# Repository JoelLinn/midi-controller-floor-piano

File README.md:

# midi-controller-floor-piano
Converts your awful sounding floor piano into a midi keyboard controller you can hook up to your synthesizers.
It uses an ARM NXP LPC1113 MCU which is hopelessly overpowered but still quite cheap.

Fits where the stock board belonged and supports the original battery, buttons and leds.
The firmware, although working great, is merely in a POC state so I would prefer to hand it out only on request.

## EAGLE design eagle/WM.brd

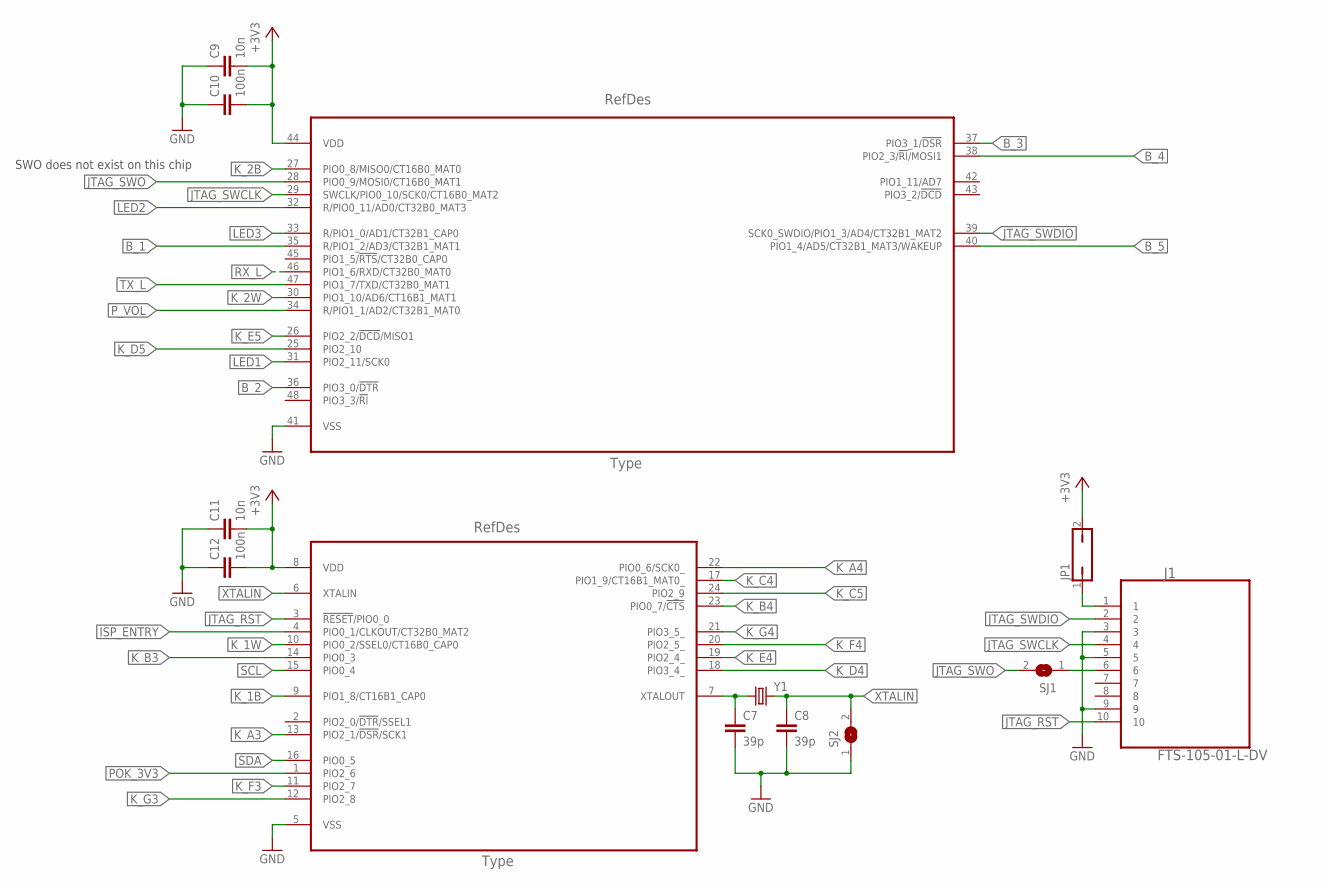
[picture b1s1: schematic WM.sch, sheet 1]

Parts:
C7, C8: 39p; C0805
C9, C11: 10n; C0805
C10, C12: 100n; C0805
J1: FTS-105-01-L-DV; SAMTEC_FTS-105-01-L-DV
JP1: JP1Q; JP1
SJ1, SJ2: SJ
U1: LPC1113FBD48/302,1; QFP50P900X900X160-48N
Y1: CRYSTALHC49UP; HC49UP

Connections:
+3V3: C9.2, C10.2, C11.2, C12.2, JP1.2, U1.8 (VDD), U1.44 (VDD); also elsewhere on the board
B_1: U1.35 (R/PIO1_2/AD3/CT32B1_MAT1); also elsewhere on the board
B_2: U1.36 (PIO3_0/!DTR!); also elsewhere on the board
B_3: U1.37 (PIO3_1/!DSR!); also elsewhere on the board
B_4: U1.38 (PIO2_3/!RI!/MOSI1); also elsewhere on the board
B_5: U1.40 (PIO1_4/AD5/CT32B1_MAT3/WAKEUP); also elsewhere on the board
GND: C7.2, C8.2, C9.1, C10.1, C11.1, C12.1, J1.3, J1.5, J1.9, SJ2.1, U1.5 (VSS), U1.41 (VSS); also elsewhere on the board
ISP_ENTRY: U1.4 (PIO0_1/CLKOUT/CT32B0_MAT2)
JTAG_RST: J1.10, U1.3 (!RESET!/PIO0_0)
JTAG_SWCLK: J1.4, U1.29 (SWCLK/PIO0_10/SCK0/CT16B0_MAT2)
JTAG_SWDIO: J1.2, U1.39 (SCK0_SWDIO/PIO1_3/AD4/CT32B1_MAT2)
JTAG_SWO: SJ1.2, U1.28 (PIO0_9/MOSI0/CT16B0_MAT1)
K_1B: U1.9 (PIO1_8/CT16B1_CAP0); also elsewhere on the board
K_1W: U1.10 (PIO0_2/SSEL0/CT16B0_CAP0); also elsewhere on the board
K_2B: U1.27 (PIO0_8/MISO0/CT16B0_MAT0); also elsewhere on the board
K_2W: U1.30 (PIO1_10/AD6/CT16B1_MAT1); also elsewhere on the board
K_A3: U1.13 (PIO2_1/!DSR!/SCK1); also elsewhere on the board
K_A4: U1.22 (PIO0_6/SCK0_); also elsewhere on the board
K_B3: U1.14 (PIO0_3); also elsewhere on the board
K_B4: U1.23 (PIO0_7/!CTS!); also elsewhere on the board
K_C4: U1.17 (PIO1_9/CT16B1_MAT0_); also elsewhere on the board
K_C5: U1.24 (PIO2_9); also elsewhere on the board
K_D4: U1.18 (PIO3_4_); also elsewhere on the board
K_D5: U1.25 (PIO2_10); also elsewhere on the board
K_E4: U1.19 (PIO2_4_); also elsewhere on the board
K_E5: U1.26 (PIO2_2/!DCD!/MISO1); also elsewhere on the board
K_F3: U1.11 (PIO2_7); also elsewhere on the board
K_F4: U1.20 (PIO2_5_); also elsewhere on the board
K_G3: U1.12 (PIO2_8); also elsewhere on the board
K_G4: U1.21 (PIO3_5_); also elsewhere on the board
LED1: U1.31 (PIO2_11/SCK0); also elsewhere on the board
LED2: U1.32 (R/PIO0_11/AD0/CT32B0_MAT3); also elsewhere on the board
LED3: U1.33 (R/PIO1_0/AD1/CT32B1_CAP0); also elsewhere on the board
unnamed: C7.1, U1.7 (XTALOUT), Y1.1
unnamed: J1.1, JP1.1
unnamed: J1.6, SJ1.1
POK_3V3: U1.1 (PIO2_6); also elsewhere on the board
P_VOL: U1.34 (R/PIO1_1/AD2/CT32B1_MAT0); also elsewhere on the board
RX_L: U1.46 (PIO1_6/RXD/CT32B0_MAT0); also elsewhere on the board
SCL: U1.15 (PIO0_4); also elsewhere on the board
SDA: U1.16 (PIO0_5); also elsewhere on the board
TX_L: U1.47 (PIO1_7/TXD/CT32B0_MAT1); also elsewhere on the board
XTALIN: C8.1, SJ2.2, U1.6 (XTALIN), Y1.2

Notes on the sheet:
SWO does not exist on this chip

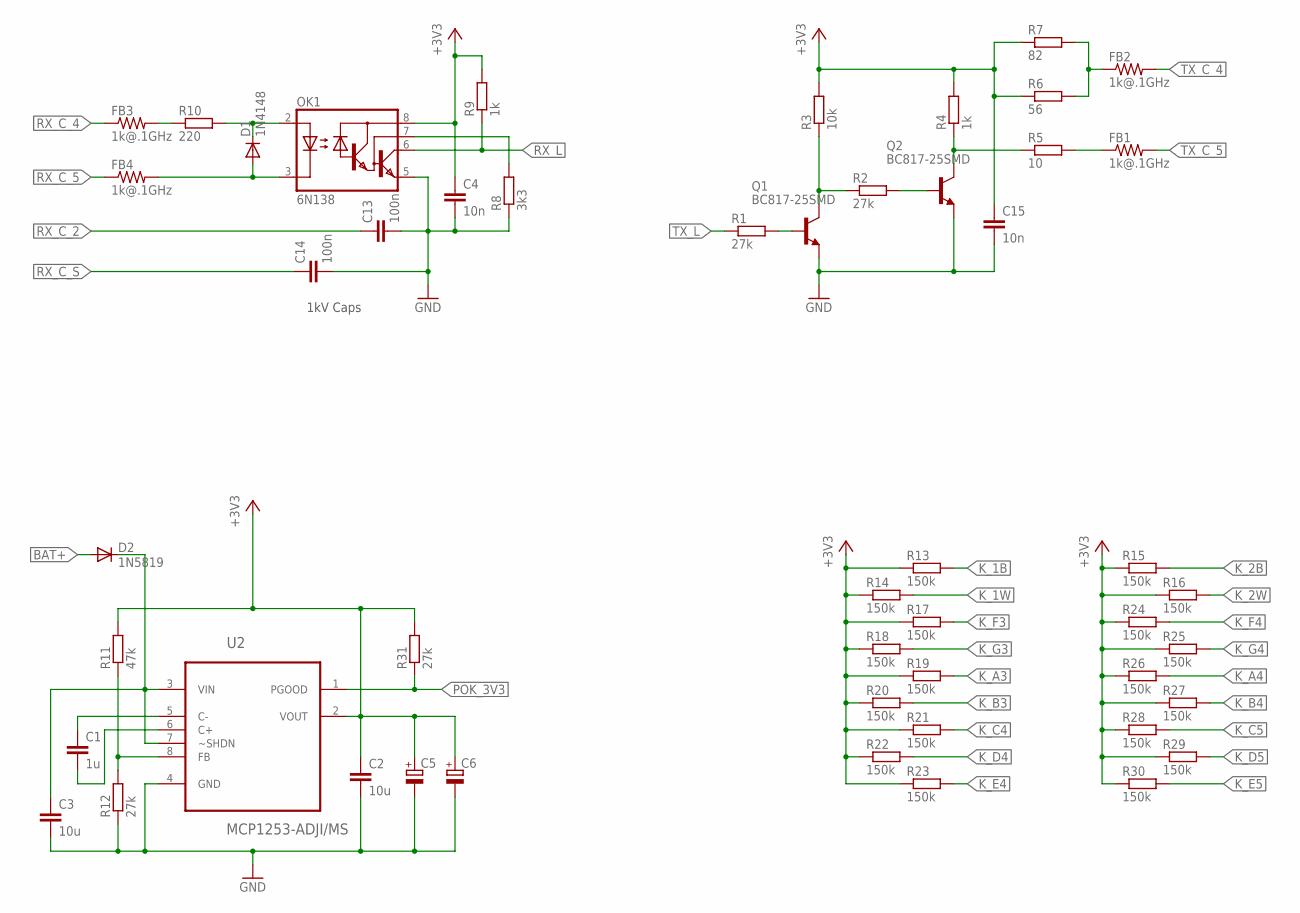
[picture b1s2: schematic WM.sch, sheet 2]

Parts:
C1: 1u; C0805
C2, C3: 10u; C0805
C4, C15: 10n; C0805
C5, C6: CPOL-EUE2.5-6; E2,5-6
C13, C14: 100n; C1210K
D1: 1N4148; SOD323-R
D2: 1N5819; SOD123
FB1, FB2, FB3, FB4: 1k@.1GHz; R0805
OK1: 6N138; DIL08
Q1, Q2: BC817-25SMD; SOT23-BEC
R1, R2, R12, R31: 27k; R0805
R3: 10k; R0805
R4, R9: 1k; R0805
R5: 10; R0805
R6: 56; R0805
R7: 82; R0805
R8: 3k3; R0805
R10: 220; R0805
R11: 47k; R0805
R13, R14, R15, R16, R17, R18, R19, R20, R21, R22, R23, R24, R25, R26, R27, R28, R29, R30: 150k; R0805
U2: MCP1253-ADJI/MS; SOP65P490X118-8N

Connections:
+3V3: C2.1, C4.1, C5.+, C6.+, C15.1, OK1.8 (VCC), R3.2, R4.2, R6.1, R7.1, R9.2, R11.2, R13.1, R14.1, R15.1, R16.1, R17.1, R18.1, R19.1, R20.1, R21.1, R22.1, R23.1, R24.1, R25.1, R26.1, R27.1, R28.1, R29.1, R30.1, R31.2, U2.2 (VOUT); also elsewhere on the board
BAT+: D2.A; also elsewhere on the board
GND: C2.2, C3.2, C4.2, C5.-, C6.-, C13.2, C14.2, C15.2, OK1.5 (GND), Q1.E, Q2.E, R8.1, R12.1, U2.4 (GND); also elsewhere on the board
K_1B: R13.2; also elsewhere on the board
K_1W: R14.2; also elsewhere on the board
K_2B: R15.2; also elsewhere on the board
K_2W: R16.2; also elsewhere on the board
K_A3: R19.2; also elsewhere on the board
K_A4: R26.2; also elsewhere on the board
K_B3: R20.2; also elsewhere on the board
K_B4: R27.2; also elsewhere on the board
K_C4: R21.2; also elsewhere on the board
K_C5: R28.2; also elsewhere on the board
K_D4: R22.2; also elsewhere on the board
K_D5: R29.2; also elsewhere on the board
K_E4: R23.2; also elsewhere on the board
K_E5: R30.2; also elsewhere on the board
K_F3: R17.2; also elsewhere on the board
K_F4: R24.2; also elsewhere on the board
K_G3: R18.2; also elsewhere on the board
K_G4: R25.2; also elsewhere on the board
unnamed: Q1.B, R1.2
unnamed: Q1.C, R2.1, R3.1
unnamed: Q2.B, R2.2
unnamed: Q2.C, R4.1, R5.1
unnamed: OK1.7 (VB), R8.2
unnamed: C1.1, U2.5 (C-)
unnamed: D1.C, OK1.2 (A), R10.2
unnamed: C1.2, U2.6 (C+)
unnamed: R11.1, R12.2, U2.8 (FB)
unnamed: FB3.2, R10.1
unnamed: D1.A, FB4.2, OK1.3 (C)
unnamed: FB1.1, R5.2
POK_3V3: R31.1, U2.1 (PGOOD); also elsewhere on the board
RX_C_2: C13.1; also elsewhere on the board
RX_C_4: FB3.1; also elsewhere on the board
RX_C_5: FB4.1; also elsewhere on the board
RX_C_S: C14.1; also elsewhere on the board
RX_L: OK1.6 (VO), R9.1; also elsewhere on the board
TX_C_4: FB2.2; also elsewhere on the board
TX_C_5: FB1.2; also elsewhere on the board
TX_H_H: FB2.1, R6.2, R7.2
TX_L: R1.1; also elsewhere on the board
UNREG+: C3.1, D2.C, U2.3 (VIN), U2.7 (~SHDN)

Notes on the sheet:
1kV Caps

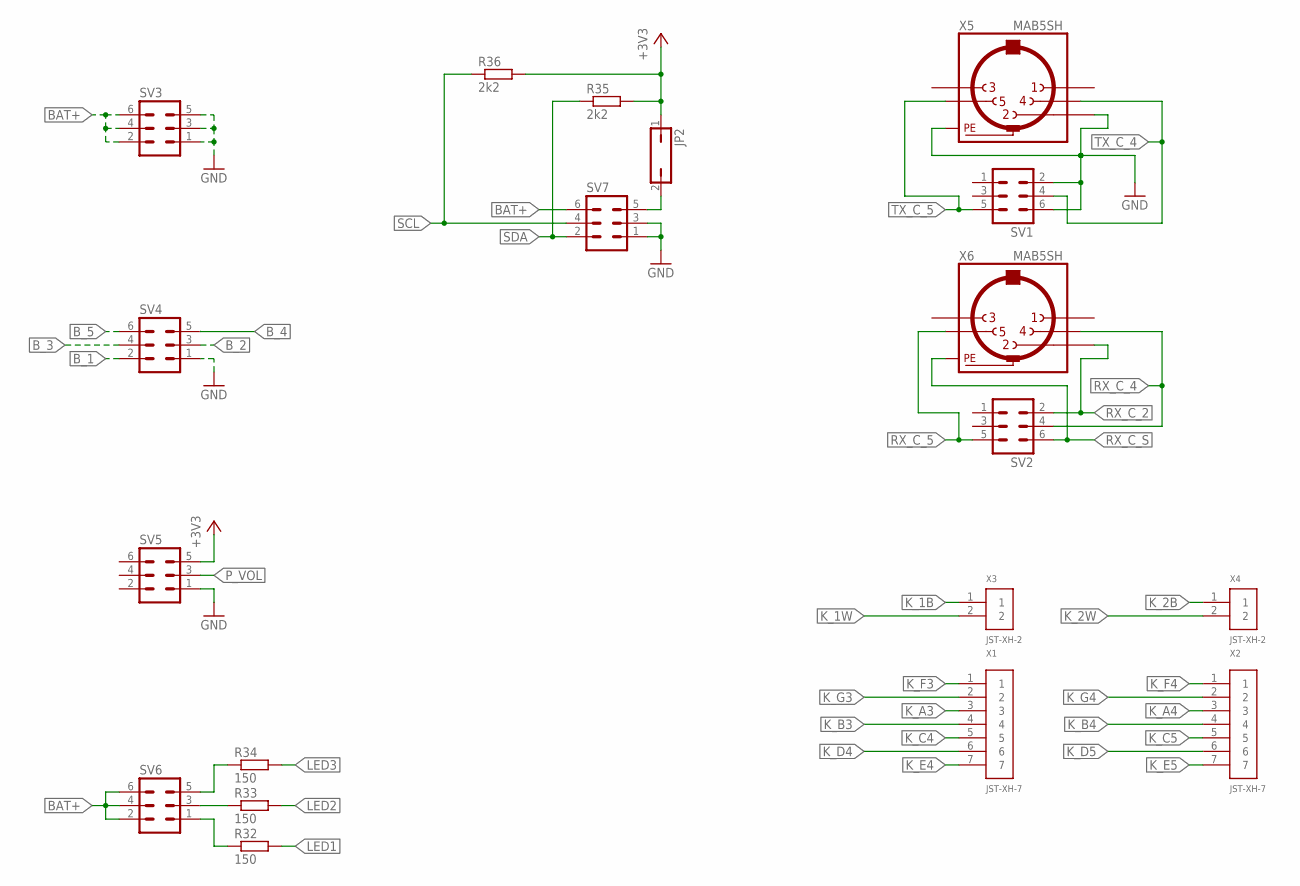
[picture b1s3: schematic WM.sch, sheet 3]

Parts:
JP2: JP1Q; JP1
R32, R33, R34: 150; R0805
R35, R36: 2k2; R0805
SV1, SV2, SV3, SV4, SV5, SV6, SV7: ML6
X1, X2: JST-XH-7
X3, X4: JST-XH-2
X5, X6: MAB5SH

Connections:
+3V3: JP2.1, R35.2, R36.2, SV5.5; also elsewhere on the board
BAT+: SV3.2, SV3.4, SV3.6, SV6.2, SV6.4, SV6.6, SV7.6; also elsewhere on the board
B_1: SV4.2; also elsewhere on the board
B_2: SV4.3; also elsewhere on the board
B_3: SV4.4; also elsewhere on the board
B_4: SV4.5; also elsewhere on the board
B_5: SV4.6; also elsewhere on the board
GND: SV1.2, SV1.6, SV3.1, SV3.3, SV3.5, SV4.1, SV5.1, SV7.1, SV7.3, X5.2, X5.PE, X5.PE@ (PE); also elsewhere on the board
K_1B: X3.1; also elsewhere on the board
K_1W: X3.2; also elsewhere on the board
K_2B: X4.1; also elsewhere on the board
K_2W: X4.2; also elsewhere on the board
K_A3: X1.3; also elsewhere on the board
K_A4: X2.3; also elsewhere on the board
K_B3: X1.4; also elsewhere on the board
K_B4: X2.4; also elsewhere on the board
K_C4: X1.5; also elsewhere on the board
K_C5: X2.5; also elsewhere on the board
K_D4: X1.6; also elsewhere on the board
K_D5: X2.6; also elsewhere on the board
K_E4: X1.7; also elsewhere on the board
K_E5: X2.7; also elsewhere on the board
K_F3: X1.1; also elsewhere on the board
K_F4: X2.1; also elsewhere on the board
K_G3: X1.2; also elsewhere on the board
K_G4: X2.2; also elsewhere on the board
LED1: R32.2; also elsewhere on the board
LED2: R33.2; also elsewhere on the board
LED3: R34.2; also elsewhere on the board
unnamed: R34.1, SV6.5
unnamed: R33.1, SV6.3
unnamed: R32.1, SV6.1
unnamed: JP2.2, SV7.5
P_VOL: SV5.3; also elsewhere on the board
RX_C_2: SV2.2, X6.2; also elsewhere on the board
RX_C_4: SV2.4, X6.4; also elsewhere on the board
RX_C_5: SV2.5, X6.5; also elsewhere on the board
RX_C_S: SV2.6, X6.PE, X6.PE@ (PE); also elsewhere on the board
SCL: R36.1, SV7.4; also elsewhere on the board
SDA: R35.1, SV7.2; also elsewhere on the board
TX_C_4: SV1.4, X5.4; also elsewhere on the board
TX_C_5: SV1.5, X5.5; also elsewhere on the board

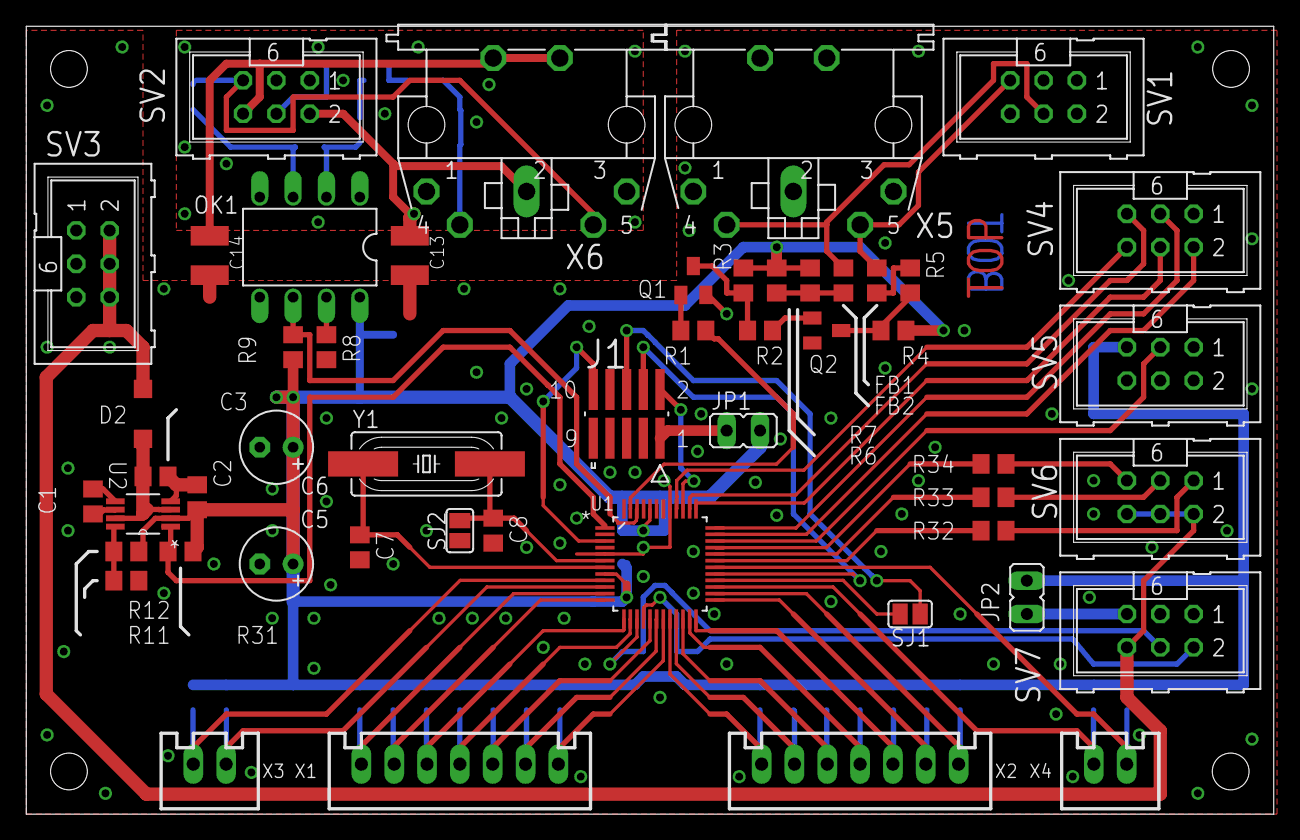
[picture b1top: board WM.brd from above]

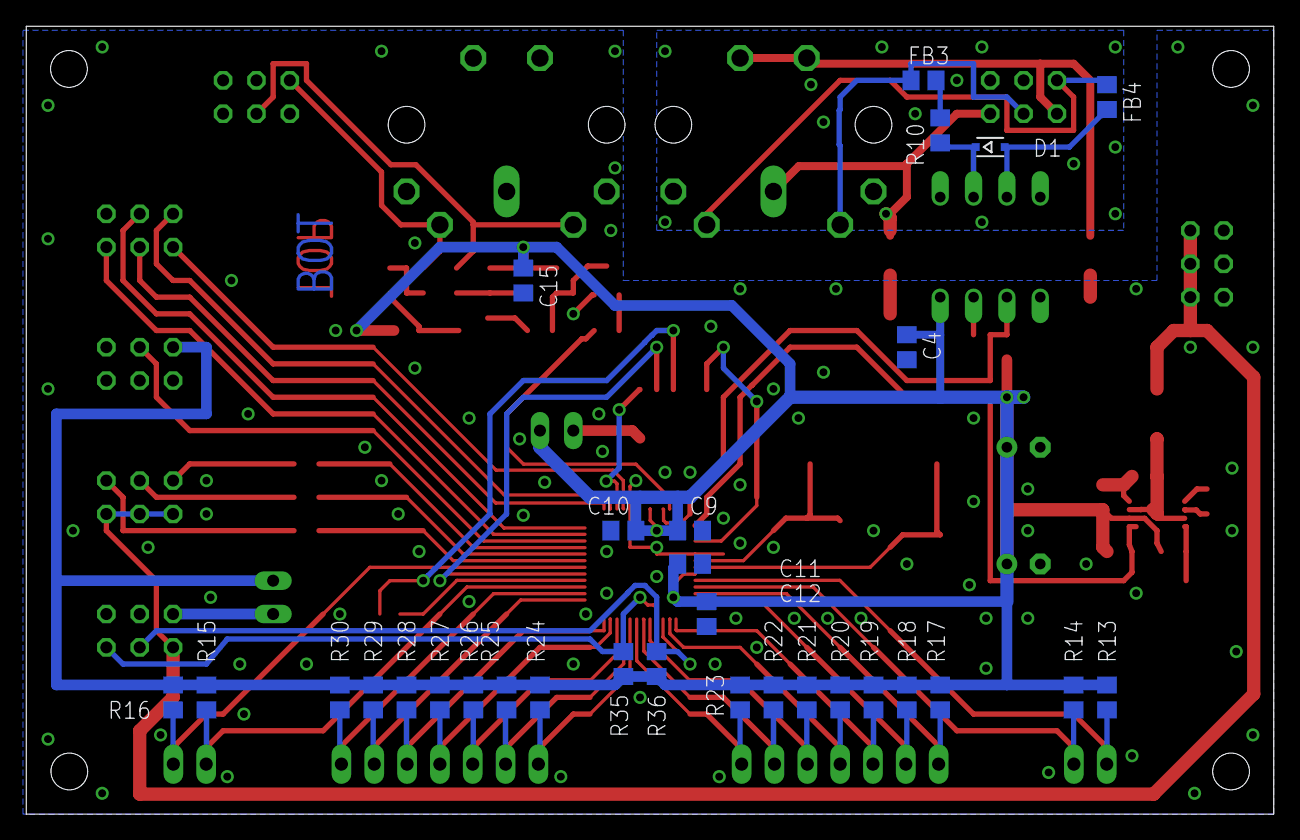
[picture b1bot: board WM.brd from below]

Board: 2 copper layers, 95.0 x 60.0 mm, 81 parts (30 on the bottom side), 67 nets.
